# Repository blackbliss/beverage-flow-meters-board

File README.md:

# Beverage Flow Meters Board #

These are the hardware design files for the project "Beverage Flow Meters", a drinks dispensing flow meter control for Beer, Wines and Spirits

### Summary ###
The board is designed specifically as a flow-measurement solution for the drink dispensing industries including beer, wines and spirits.

### How do I get set up? ###

    $ git clone https://github.com/blackbliss/beverage-flow-meters-board.git

### What's included ###

* **Datasheets** — Datasheets for the various components.
* **EAGLE** — Schematic and board files
* **Gerber** — Complete set of Gerber files for the current version of the project.

### Hardware connections ###

    +-----------------+
    |          D0 [16]| ---> Status LED
    |          D1 [05]| ---> I2C SDA (to PCF8574)
    |          D2 [04]| ---> I2C SCL (to PCF8574)
    |          D4 [02]| <--- Ball sensor (water presence)
    |              3V3| ----
    |              GND| ----
    |          D5 [14]| <--- Distance sensor TRIG
    |          D6 [12]| <--- Distance sensor ECHO
    |          D7 [13]| ----
    |          D8 [15]| ----
    |          D9 [03]| ----
    |          D10[01]| ----
    |              GND| ----
    |              3V3| ----
    +-----------------+

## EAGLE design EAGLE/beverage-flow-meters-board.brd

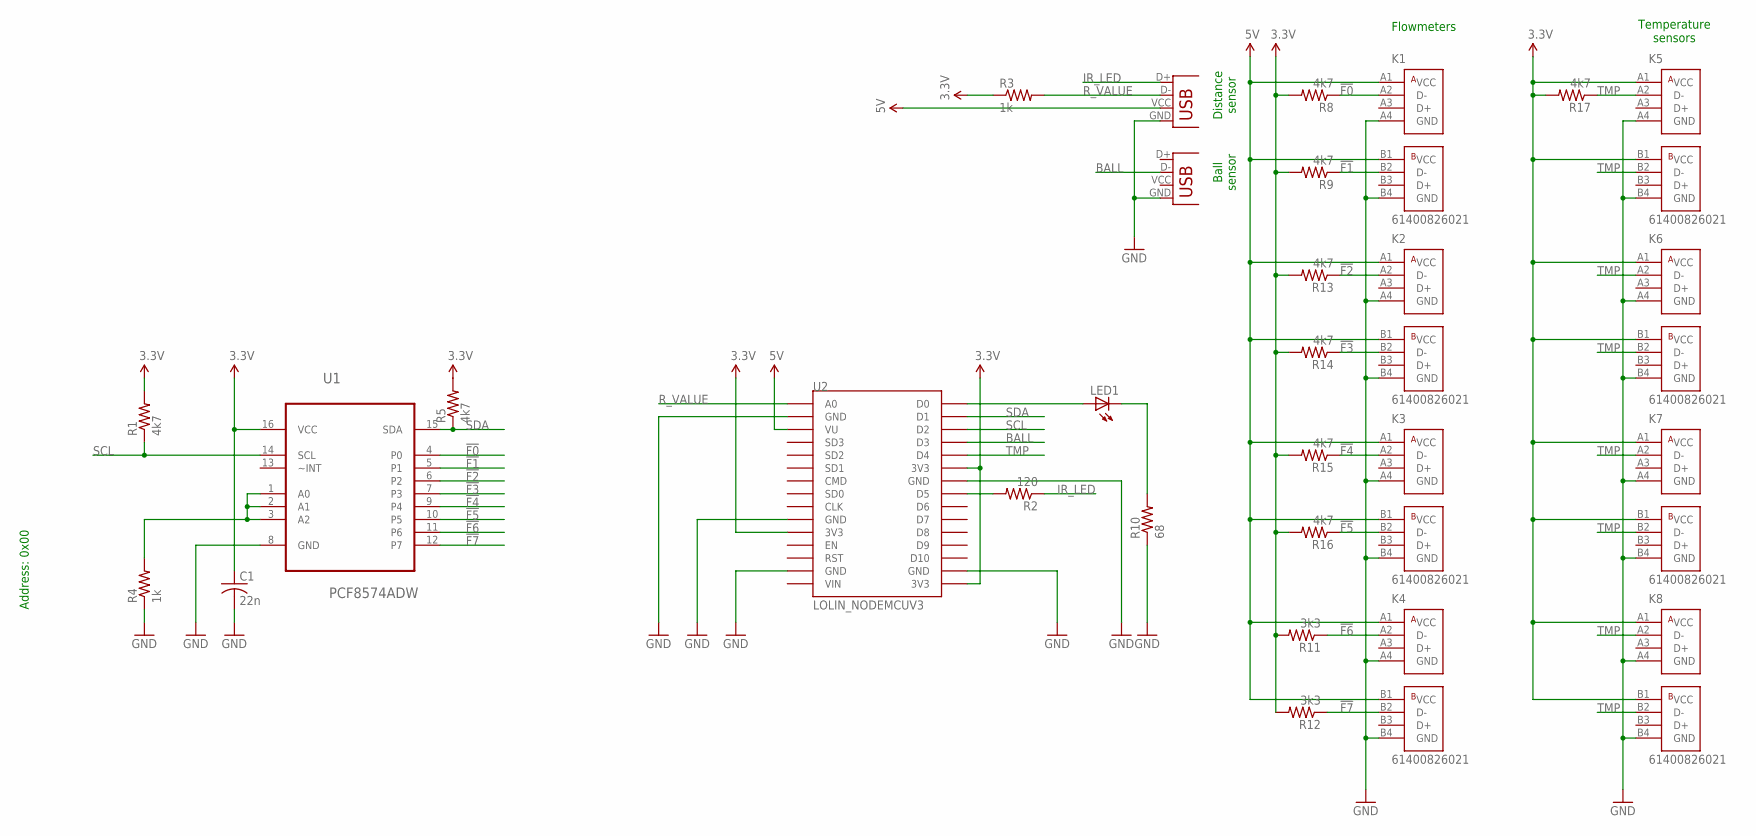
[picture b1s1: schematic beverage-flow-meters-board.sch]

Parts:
C1: 22n; C1206
JP1, JP2: USB-A-H; USB-A-VERT
K1, K2, K3, K4, K5, K6, K7, K8: 61400826021
LED1: LEDCHIP-LED0603; CHIP-LED0603
R1, R5, R8, R9, R13, R14, R15, R16, R17: 4k7; R0603
R2: 120; R0603
R3, R4: 1k; R0603
R10: 68; R0603
R11, R12: 3k3; R0603
U1: PCF8574ADW; SOIC127P1030X265-16N
U2: LOLIN_NODEMCUV3; ESP12E_DEVKIT_CHINA

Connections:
3.3V: C1.1, K5.A1 (VCC), K5.B1 (VCC), K6.A1 (VCC), K6.B1 (VCC), K7.A1 (VCC), K7.B1 (VCC), K8.A1 (VCC), K8.B1 (VCC), R1.2, R3.1, R5.2, R8.2, R9.2, R11.2, R12.2, R13.2, R14.2, R15.2, R16.2, R17.2, U1.16 (VCC), U2.3V3@0 (3V3), U2.3V3@1 (3V3), U2.3V3@2 (3V3)
5V: JP1.VCC (VBUS), K1.A1 (VCC), K1.B1 (VCC), K2.A1 (VCC), K2.B1 (VCC), K3.A1 (VCC), K3.B1 (VCC), K4.A1 (VCC), K4.B1 (VCC), U2.VU
!F0: K1.A2 (D-), R8.1, U1.4 (P0)
!F1: K1.B2 (D-), R9.1, U1.5 (P1)
!F2: K2.A2 (D-), R13.1, U1.6 (P2)
!F3: K2.B2 (D-), R14.1, U1.7 (P3)
!F4: K3.A2 (D-), R15.1, U1.9 (P4)
!F5: K3.B2 (D-), R16.1, U1.10 (P5)
!F6: K4.A2 (D-), R11.1, U1.11 (P6)
!F7: K4.B2 (D-), R12.1, U1.12 (P7)
BALL: JP2.D-, U2.D3
GND: C1.2, JP1.GND, JP2.GND, K1.A4 (GND), K1.B4 (GND), K2.A4 (GND), K2.B4 (GND), K3.A4 (GND), K3.B4 (GND), K4.A4 (GND), K4.B4 (GND), K5.A4 (GND), K5.B4 (GND), K6.A4 (GND), K6.B4 (GND), K7.A4 (GND), K7.B4 (GND), K8.A4 (GND), K8.B4 (GND), R4.1, R10.1, U1.8 (GND), U2.GND@0 (GND), U2.GND@1 (GND), U2.GND@2 (GND), U2.GND@3 (GND), U2.GND@4 (GND)
IR_LED: JP1.D+, R2.1
unnamed: R4.2, U1.1 (A0), U1.2 (A1), U1.3 (A2)
unnamed: R2.2, U2.D5
unnamed: LED1.A, U2.D0
unnamed: LED1.C, R10.2
R_VALUE: JP1.D-, R3.2, U2.A0
SCL: R1.1, U1.14 (SCL), U2.D2
SDA: R5.1, U1.15 (SDA), U2.D1
TMP: K5.A2 (D-), K5.B2 (D-), K6.A2 (D-), K6.B2 (D-), K7.A2 (D-), K7.B2 (D-), K8.A2 (D-), K8.B2 (D-), R17.1, U2.D4

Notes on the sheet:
Address: 0x00
Flowmeters
Temperature sensors
Distance sensor
Ball sensor

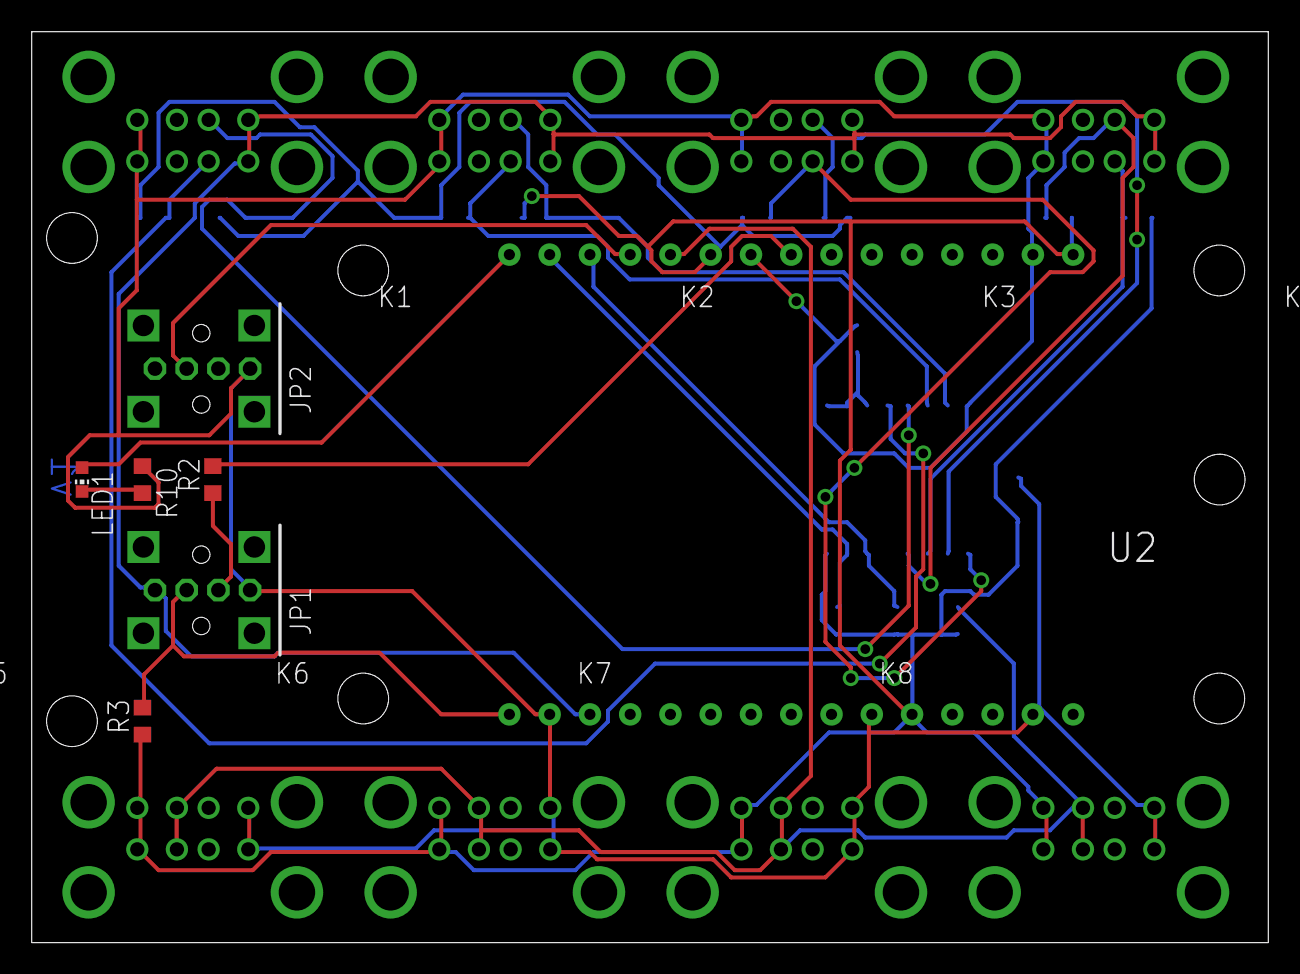
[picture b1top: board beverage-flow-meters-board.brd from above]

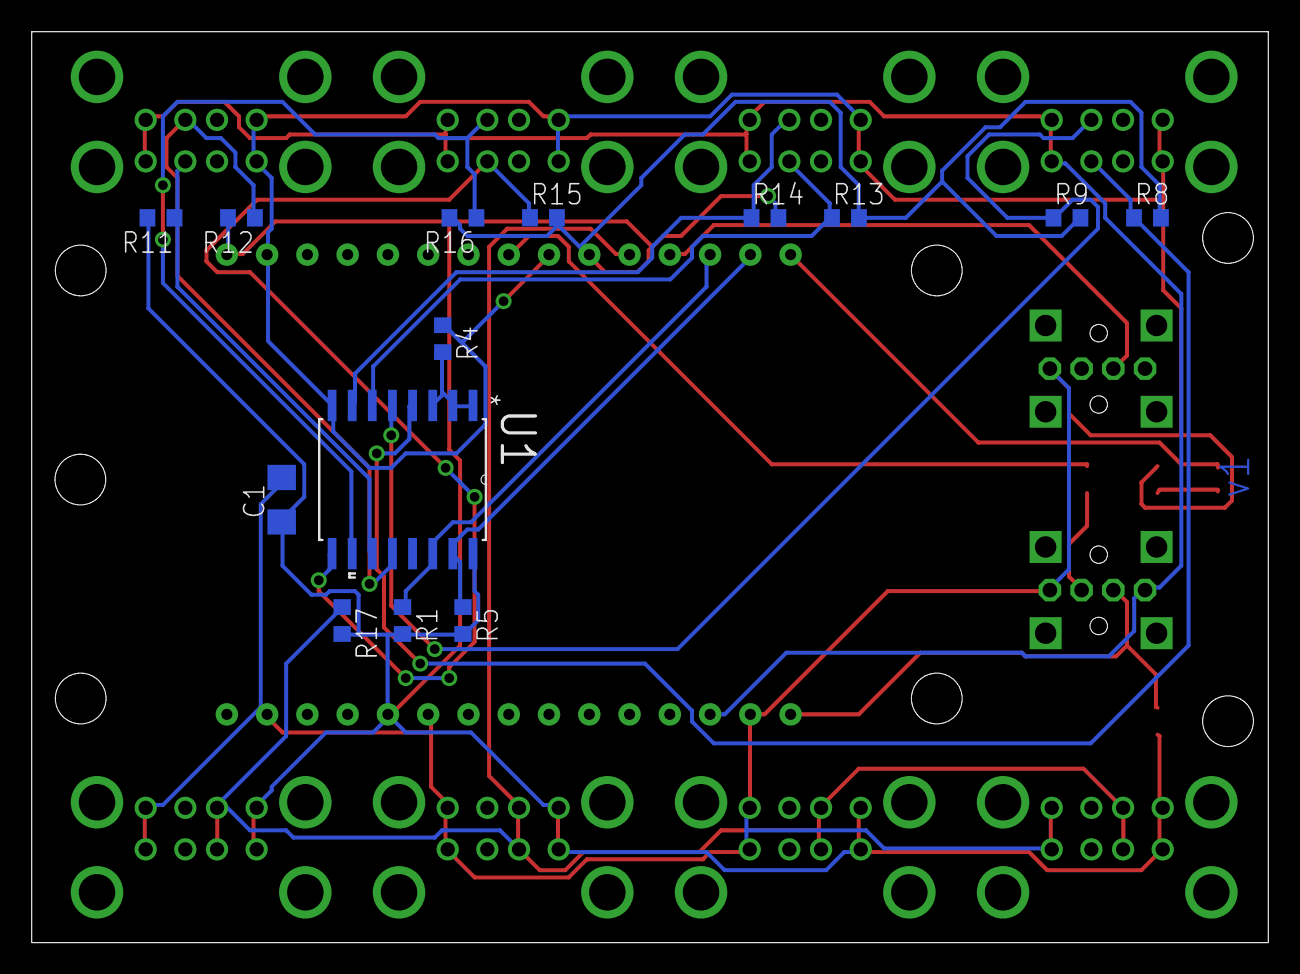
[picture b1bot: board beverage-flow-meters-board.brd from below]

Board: 2 copper layers, 78.0 x 57.5 mm, 29 parts (14 on the bottom side), 21 nets.

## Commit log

2016-08-11 Initial commit with contributors
2016-08-11 Added board and schematic for v1
2016-08-11 Added datasheets
2016-08-11 Minor changes
2016-08-11 README.md edited online with Bitbucket
2016-08-11 Updated board with 3 holes
2016-08-11 Added bill of materials
2016-08-23 Added version number v1 to the board
2016-08-23 Added image file with the map of the used pins
2018-03-21 Update README file
2018-03-21 Add contribution guide
2018-03-21 Change project global attributes
2018-03-21 Rename bom files
2018-03-21 Remove epf file
2018-03-21 Add Hardware connections chapter to README
2018-03-21 Update datasheets
2018-03-21 Minor changes in README: formatting

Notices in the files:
parts and their libraries:
Wuerth_Elektronik_eiCan_Communication_Co: Copyright: Würth Elektronik
SparkFun-Aesthetics: Licensing: Creative Commons ShareAlike 4.0 International - https://creativecommons.org/licenses/by-sa/4.0
